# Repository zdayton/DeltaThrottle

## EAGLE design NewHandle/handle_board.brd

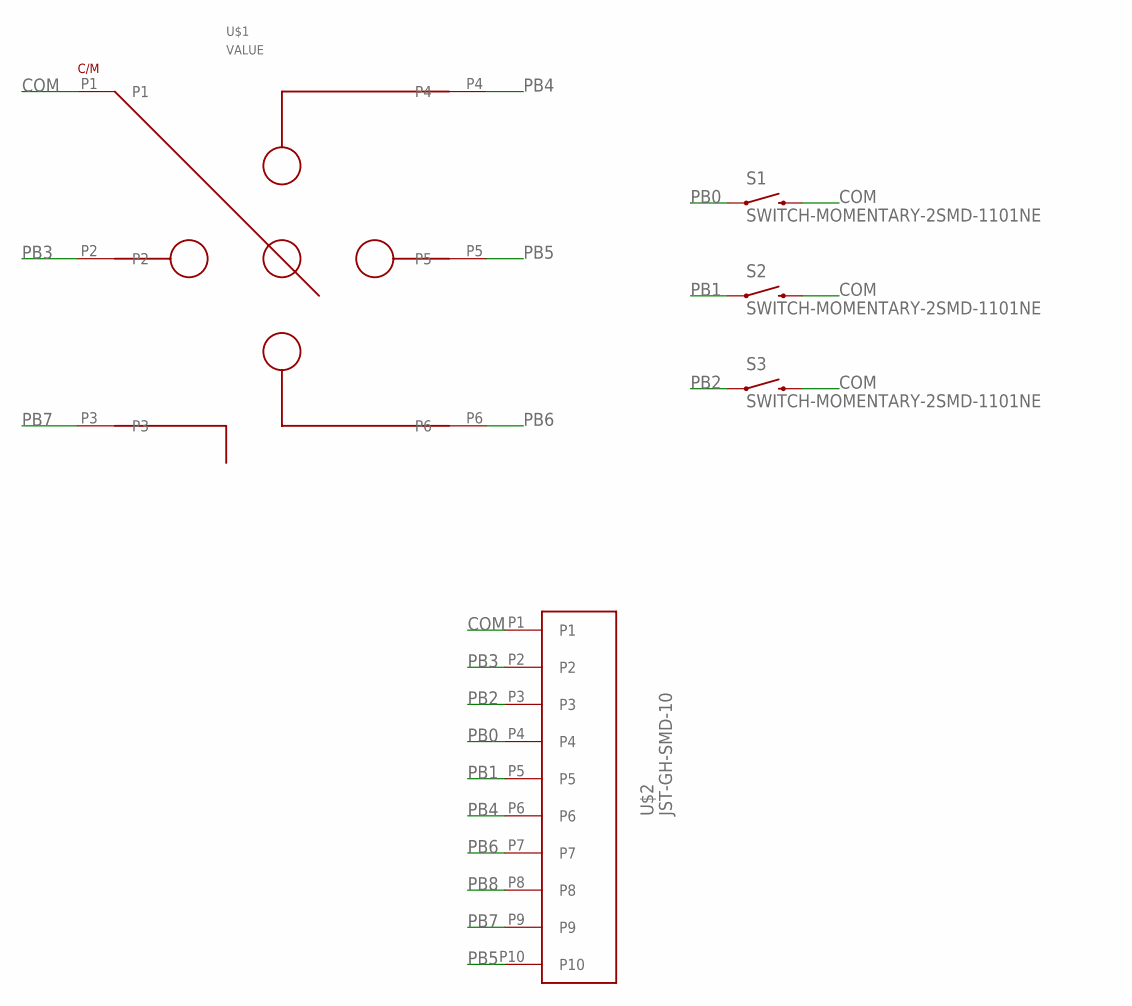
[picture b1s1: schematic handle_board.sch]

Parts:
S1, S2, S3: SWITCH-MOMENTARY-2SMD-1101NE; TACTILE-SWITCH-1101NE
U$1: JS_5208_HAT
U$2: JST-GH-SMD-10

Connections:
COM: S1.2, S2.2, S3.2, U$1.P1, U$2.P1
PB0: S1.1, U$2.P4
PB1: S2.1, U$2.P5
PB2: S3.1, U$2.P3
PB3: U$1.P2, U$2.P2
PB4: U$1.P4, U$2.P6
PB5: U$1.P5, U$2.P10
PB6: U$1.P6, U$2.P7
PB7: U$1.P3, U$2.P9
PB8: U$2.P8

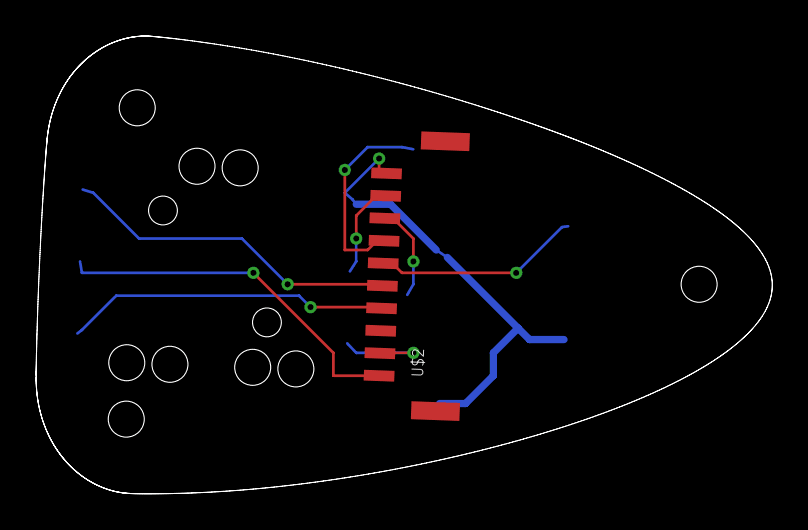
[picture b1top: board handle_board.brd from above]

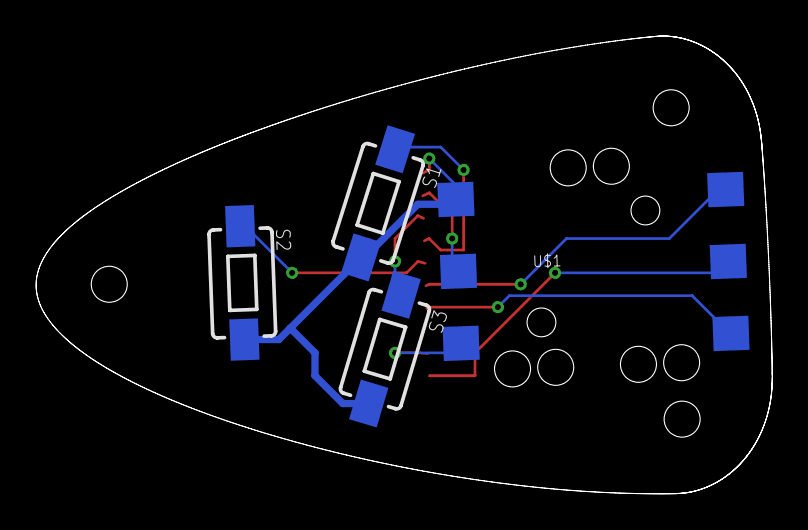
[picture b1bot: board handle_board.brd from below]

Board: 2 copper layers, 40.9 x 25.4 mm, 5 parts (4 on the bottom side), 9 nets.

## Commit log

2015-01-05 Delta Throttle first commit
2015-01-05 Revert "Delta Throttle first commit"
    This reverts commit c3c13f94a5e389d4353f4395c80c7f0514b5f560.
2015-01-05 Revert "Revert "Delta Throttle first commit""
    This reverts commit a3af0dd5c1a73b39d30ae8348f704661ec14bb18.
2015-01-05 Revert "Revert "Revert "Delta Throttle first commit"""
    This reverts commit 1764c813610cc91e2aa7da25dd8de1d8d345e313.
2015-01-05 Delta Throttle
2015-03-03 Drawing
    Base drawing
2015-03-06 drawings
    Base and pivot arm
2015-03-28 Build instructions to include arduino version
2015-05-07 New Handle
    STL and eagle file for new handle revision
2015-11-09 handle source files

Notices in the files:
parts and their libraries:
SparkFun-Electromechanical: Licensing: Creative Commons ShareAlike 4.0 International - https://creativecommons.org/licenses/by-sa/4.0
